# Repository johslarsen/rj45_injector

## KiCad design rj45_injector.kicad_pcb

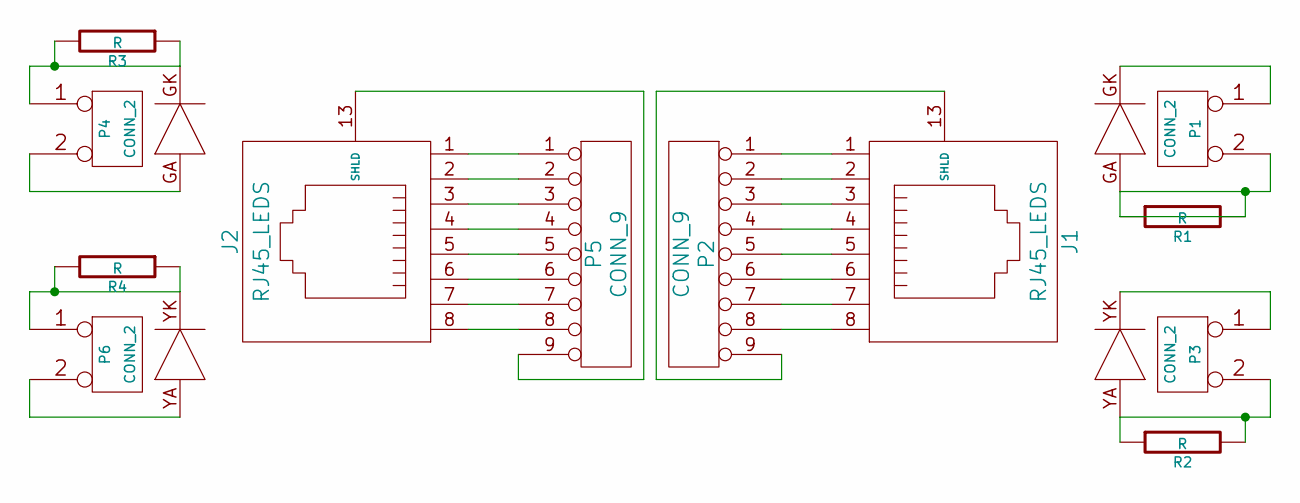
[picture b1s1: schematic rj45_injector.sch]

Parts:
J1, J2: RJ45_LEDS
P1, P3, P4, P6: CONN_2
P2, P5: CONN_9
R1, R2, R3, R4: R

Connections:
unnamed: J1.1, P2.1
unnamed: J1.2, P2.2
unnamed: J1.3, P2.3
unnamed: J1.4, P2.4
unnamed: J1.5, P2.5
unnamed: J1.6, P2.6
unnamed: J1.7, P2.7
unnamed: J1.8, P2.8
unnamed: J1.13 (SHLD), P2.9
unnamed: J1.GA, P1.2 (PM), R1.1, R1.2
unnamed: J1.GK, P1.1
unnamed: J1.YA, P3.2 (PM), R2.1, R2.2
unnamed: J1.YK, P3.1
unnamed: J2.1, P5.1
unnamed: J2.2, P5.2
unnamed: J2.3, P5.3
unnamed: J2.4, P5.4
unnamed: J2.5, P5.5
unnamed: J2.6, P5.6
unnamed: J2.7, P5.7
unnamed: J2.8, P5.8
unnamed: J2.13 (SHLD), P5.9
unnamed: J2.GA, P4.2 (PM)
unnamed: J2.GK, P4.1, R3.1, R3.2
unnamed: J2.YA, P6.2 (PM)
unnamed: J2.YK, P6.1, R4.1, R4.2

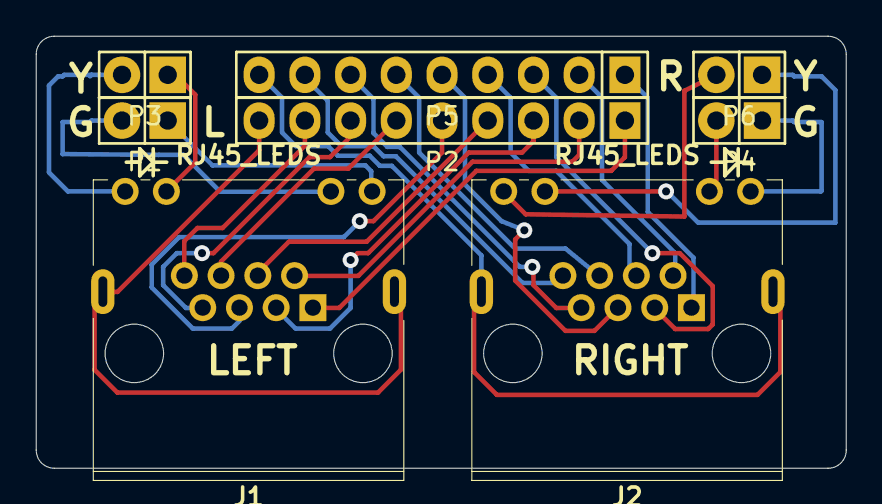
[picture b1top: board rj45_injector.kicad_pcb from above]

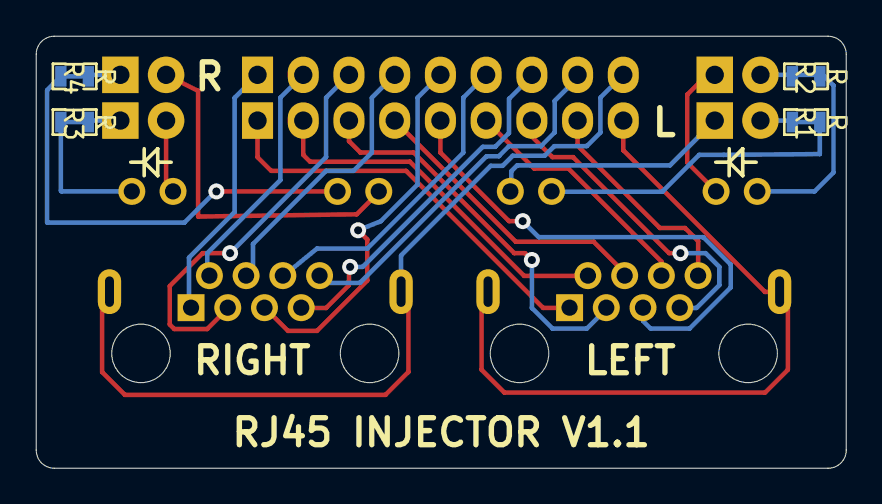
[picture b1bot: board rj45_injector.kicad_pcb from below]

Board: 2 copper layers, 45.0 x 24.0 mm, 12 parts (4 on the bottom side), 26 nets.

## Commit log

2015-01-11 added UNLICENSE
2015-01-11 added lib/Connectors.pretty submodule
2015-01-11 completed the board
2015-01-14 aligned board to 1mm and rounded corners
2015-01-14 changed to relative submodules and removed accidentally added legacy components library submodule
2015-02-07 added v1.0 output files
2015-02-08 fixed LEFT,RIGHT label mismatch (R,L respectively)
2015-02-08 updated RJ45 connector modules
